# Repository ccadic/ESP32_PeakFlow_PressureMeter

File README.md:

# ESP32_PeakFlow_PressureMeter
Kicad prototype for a medical peak flow / pressure meter

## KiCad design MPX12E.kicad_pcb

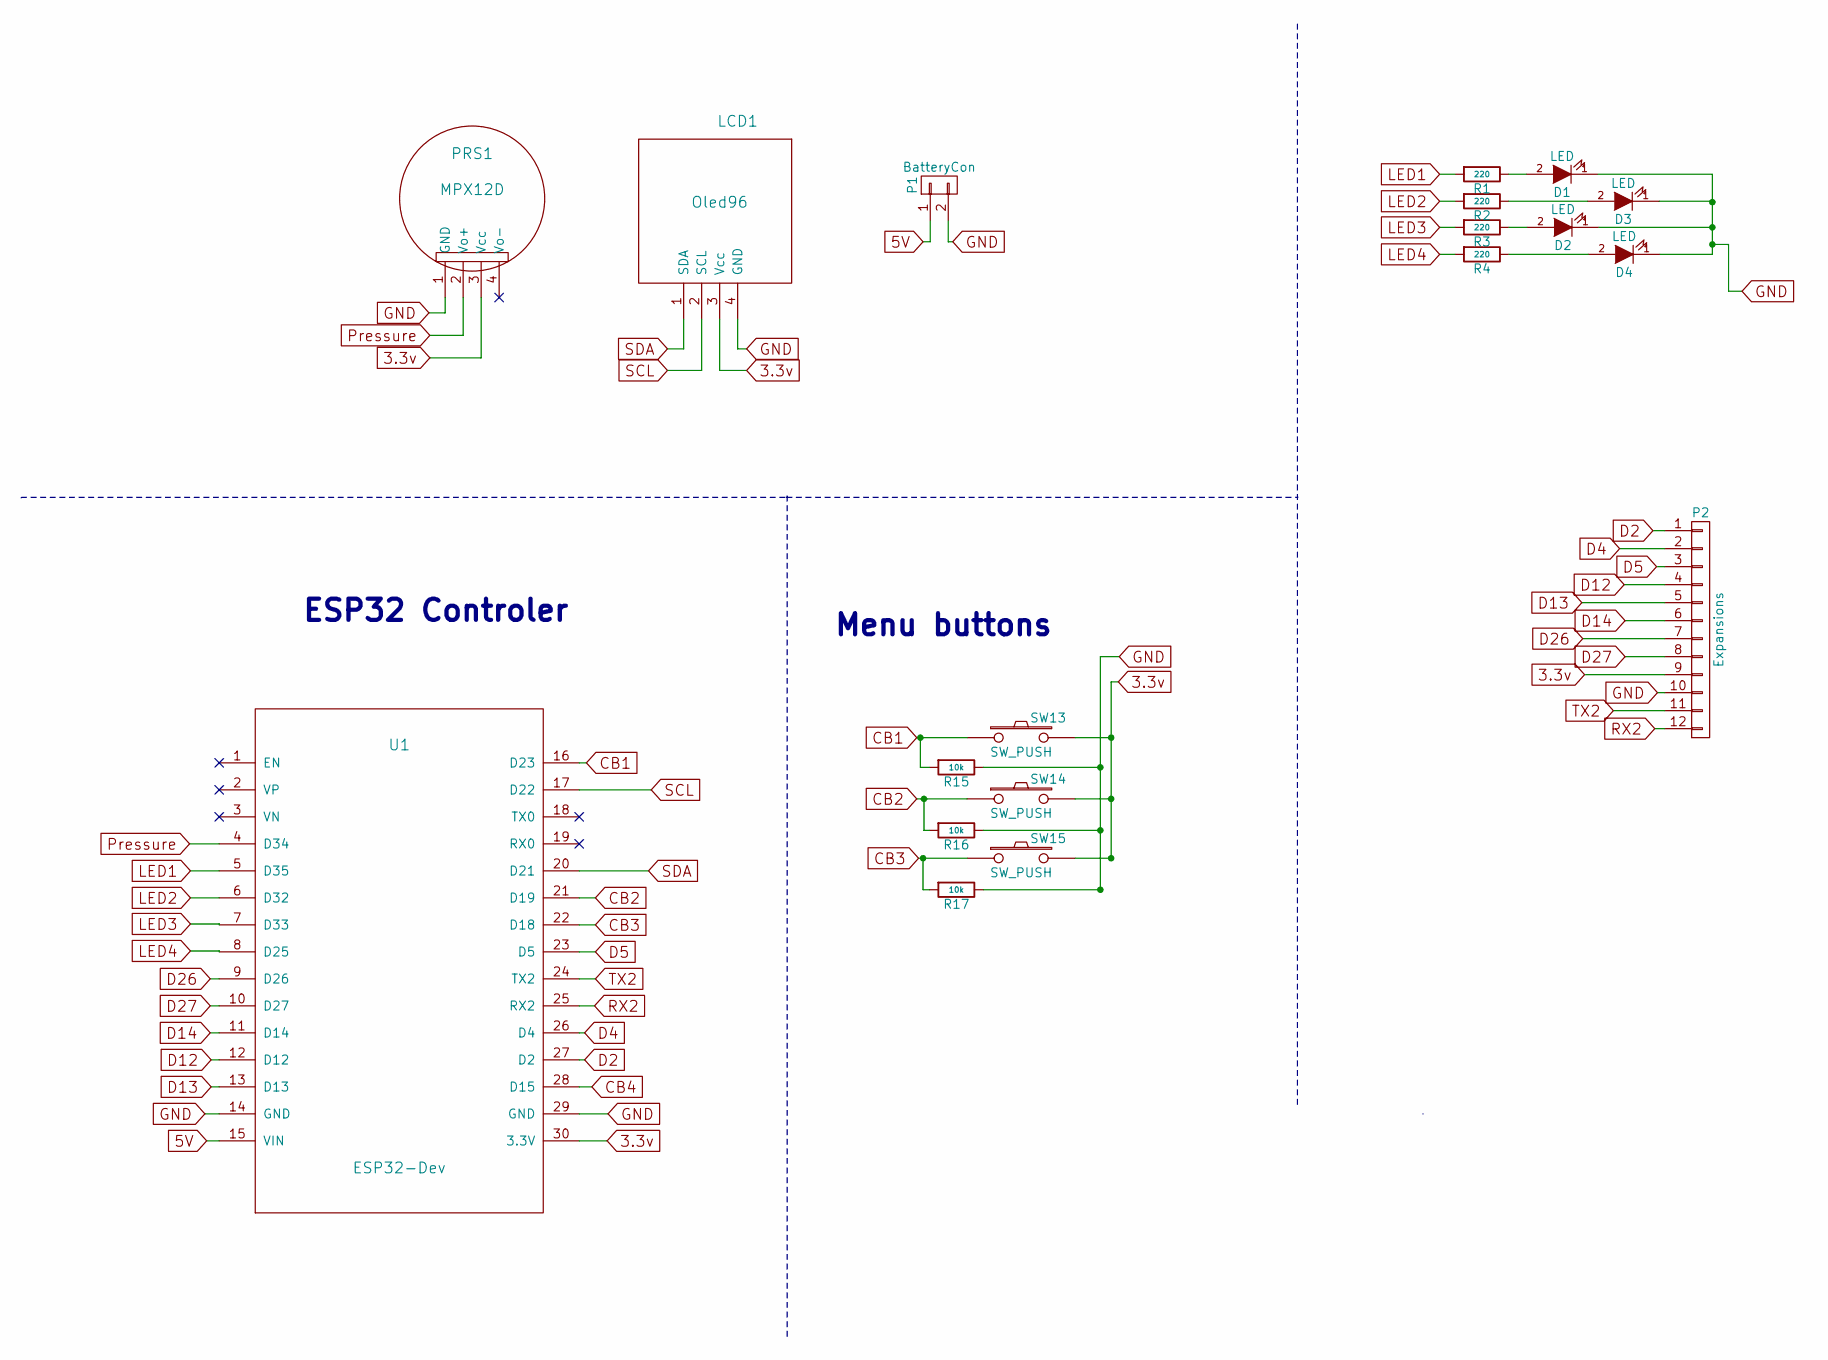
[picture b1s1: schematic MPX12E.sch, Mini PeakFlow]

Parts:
D1, D2, D3, D4: LED; LED_D3.0mm
LCD1: Oled96
P1: BatteryCon; Socket_Strip_Straight_1x02_Pitch2.54mm
P2: Expansions; Socket_Strip_Straight_1x12_Pitch2.54mm
PRS1: MPX12D; MPX12D_straight
R1, R2, R3, R4: 220; R_1206_HandSoldering
R15, R16, R17: 10k; R_1206_HandSoldering
SW13, SW14, SW15: SW_PUSH; SW_SPST_B3S-1000
U1: ESP32-Dev; ESP32-DEV

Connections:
3.3v: LCD1.3 (Vcc), P2.9, PRS1.3 (Vcc), SW13.2, SW14.2, SW15.2, U1.30 (3.3V)
5V: P1.1, U1.15 (VIN)
CB1: R15.2, SW13.1, U1.16 (D23)
CB2: R16.2, SW14.1, U1.21 (D19)
CB3: R17.2, SW15.1, U1.22 (D18)
D2: P2.1, U1.27 (D2)
D4: P2.2, U1.26 (D4)
D5: P2.3, U1.23 (D5)
D12: P2.4, U1.12 (D12)
D13: P2.5, U1.13 (D13)
D14: P2.6, U1.11 (D14)
D26: P2.7, U1.9 (D26)
D27: P2.8, U1.10 (D27)
GND: D1.1 (K), D2.1 (K), D3.1 (K), D4.1 (K), LCD1.4 (GND), P1.2, P2.10, PRS1.1 (GND), R15.1, R16.1, R17.1, U1.14 (GND), U1.29 (GND)
LED1: R1.2, U1.5 (D35)
LED2: R2.2, U1.6 (D32)
LED3: R3.2, U1.7 (D33)
LED4: R4.2, U1.8 (D25)
unnamed: D1.2 (A), R1.1
unnamed: D2.2 (A), R3.1
unnamed: D3.2 (A), R2.1
unnamed: D4.2 (A), R4.1
Pressure: PRS1.2 (Vo+), U1.4 (D34)
RX2: P2.12, U1.25 (RX2)
SCL: LCD1.2 (SCL), U1.17 (D22)
SDA: LCD1.1 (SDA), U1.20 (D21)
TX2: P2.11, U1.24 (TX2)

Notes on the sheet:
Menu buttons
ESP32 Controler

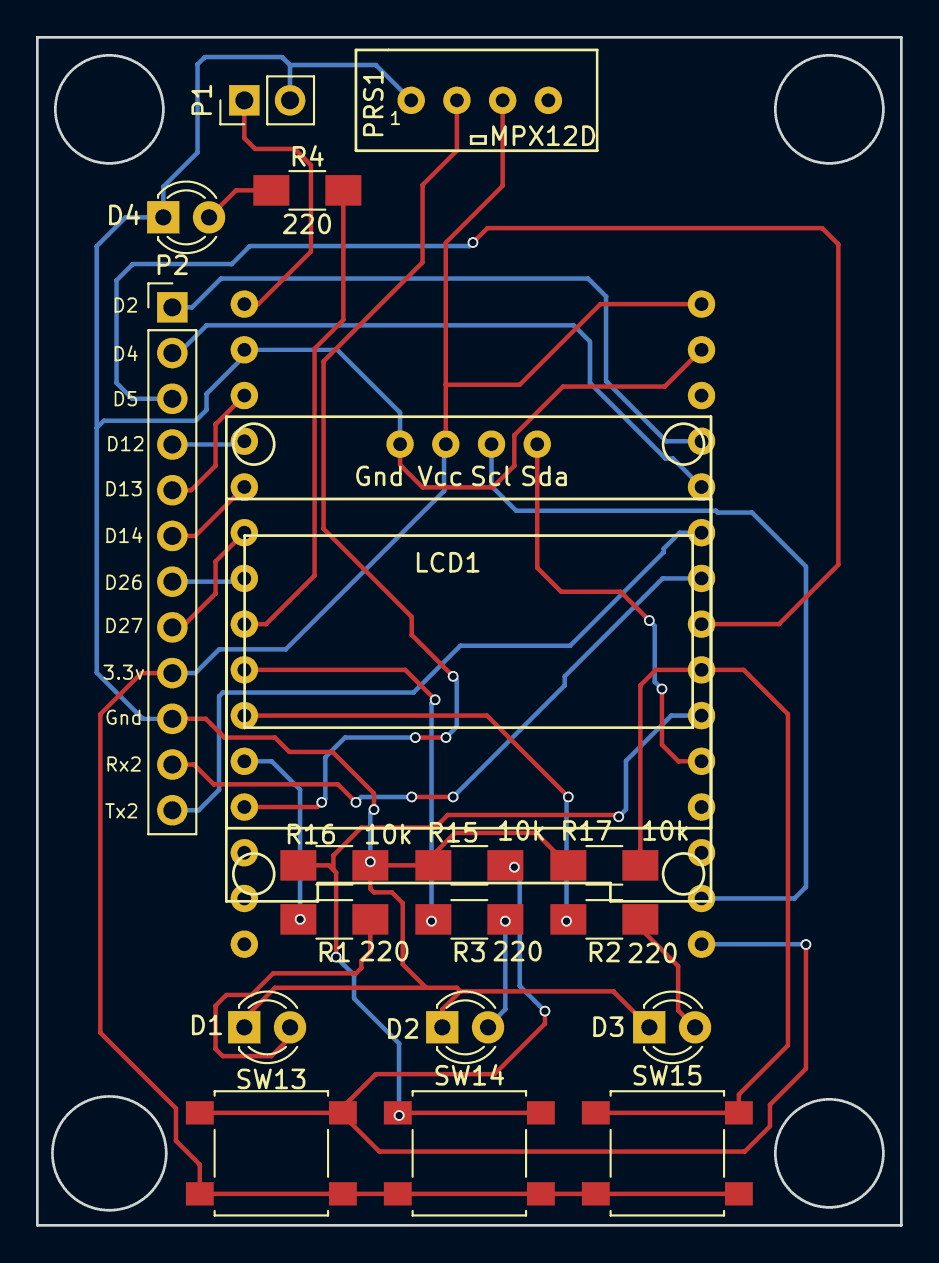
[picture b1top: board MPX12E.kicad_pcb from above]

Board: 2 copper layers, 48.0 x 66.0 mm, 19 parts (1 on the bottom side), 27 nets.
